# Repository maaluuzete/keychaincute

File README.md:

# Keychain Cute

This project is exactly what it sounds like: a keychain that is also a PCB. I really wanted to make something small, fun, and tangible, and what better way to do that than turning a PCB into a keychain? It’s simple, it lights up, and it’s a tiny excuse to say “yeah, I designed this board myself” 😌 This is a USB-powered LED keychain made entirely from a PCB. When you plug it into a USB port, the LED turns on.

## Screenshots

## Project Structure
```
/
├── images/
│   ├── key_3d.png      
│   ├── key_pcb.png    
│   └── key_schematic.png  
│
├── pcb/
│   ├── gerbers/            # Manufacturing files
│   ├── keychainmalu.kicad_pcb
│   ├── keychainmalu.kicad_pro
│   └── keychainmalu.kicad_sch
│
├── LICENSE
└── README.md
```
## BOM
| Item        | URL | Quantity | Unit Price ($) | Total Price ($) | Running Total (With tax) $ |
|------------|-----|----------|----------------|-----------------|-----------------------------|
| USB B Micro | https://www.aliexpress.com/p/tesla-landing/index.html?scenario=c_ppc_item_bridge&productId=1005004280682450&_immersiveMode=true&withMainCard=true&src=google&aff_platform=true&isdl=y&src=google&albch=shopping&acnt=768-202-3196&isdl=y&slnk=&plac=&mtctp=&albbt=Google_7_shopping&aff_platform=google&aff_short_key=UneMJZVf&gclsrc=aw.ds&&albagn=888888&&ds_e_adid=&ds_e_matchtype=&ds_e_device=c&ds_e_network=x&ds_e_product_group_id=&ds_e_product_id=pt1005004280682450&ds_e_product_merchant_id=419595364&ds_e_product_country=BR&ds_e_product_language=pt&ds_e_product_channel=online&ds_e_product_store_id=&ds_url_v=2&albcp=21106536414&albag=&isSmbAutoCall=false&needSmbHouyi=false&gad_source=1&gad_campaignid=21106537179&gbraid=0AAAAAC_WlP-md_4YkkXvbSPrNxDPgsh7s&gclid=Cj0KCQiA18DMBhDeARIsABtYwT3UV9D02O19ZPgyw6MjiTx4fNWhK0_kbgUcWJ6lp5j0MogO0UyYT0MaAqDiEALw_wcB | 1 | 1,06 | 1,06 | 7,08 |
| LED | https://shopee.com.br/product/413370384/18345362456 | 1 | 1,34 | 1,34 | 1,34 |
| PCB | https://cart.jlcpcb.com/ | 1 | 2,2 | 2,2 | 12,58 |

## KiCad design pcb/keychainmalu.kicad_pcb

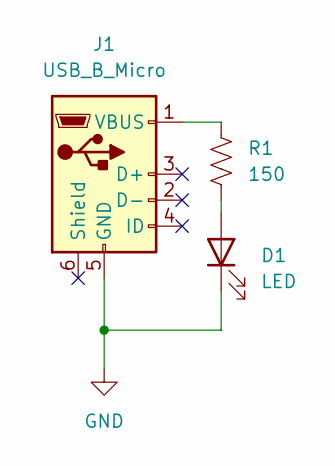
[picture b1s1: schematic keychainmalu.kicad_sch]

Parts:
D1: LED; LED_0402_1005Metric_Pad0.77x0.64mm_HandSolder
J1: USB_B_Micro; USB_Micro-B_Amphenol_10103594-0001LF_Horizontal
R1: 150; R_0603_1608Metric

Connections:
GND: D1.1 (K), J1.5 (GND)
unnamed: D1.2 (A), R1.2
unnamed: J1.1 (VBUS), R1.1

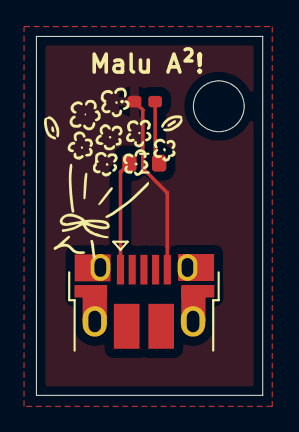
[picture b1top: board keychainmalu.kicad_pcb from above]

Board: 2 copper layers, 12.6 x 19.9 mm, 3 parts (0 on the bottom side), 3 nets.

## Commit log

2026-01-28 Add schematic for keychain project with USB Micro connector and LED
    - Created a new schematic file for the keychain project.
    - Added USB Micro Type B connector with appropriate pin configuration and properties.
    - Included an LED component with defined properties and connections.
    - Added a resistor symbol with specified value and footprint.
    - Defined global ground symbol for power connections.
    - Established wire connections between components in the schematic.
2026-01-28 Update README with project details and structure
    Added project description, structure, and images.
2026-01-28 images
2026-02-15 Add BOM section to README
    Added a Bill of Materials (BOM) section with item details.

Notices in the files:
README.md:
License: MIT
